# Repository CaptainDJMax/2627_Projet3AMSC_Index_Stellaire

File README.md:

## Project Description
The "Stellar Index" is an autonomous and aesthetic mechanical arm, designed to point in real time at a specific celestial object selected via a mobile or web app. Whether it's a planet, a star, the International Space Station (ISS), or a galaxy, the arm tracks the object continuously.

If the object goes below the horizon, the arm will point toward the ground. Designed with premium materials, it serves as both an educational science tool and an indoor kinetic art piece.

---

## Specifications & Technical Challenges

Here is the list of project requirements, along with recommended hardware choices and the technical challenges to anticipate.

### 1. Continuous 360° Celestial Tracking
**Description:** The arm must dynamically target a celestial object and compensate for Earth's rotation in real time, with no limits on its rotation.
- **Hardware:** A base motor for the Azimuth (horizontal) axis, a motor for the Elevation (vertical) axis, and a **slip ring** placed in the center of the rotation axis.
- **Difficulty:** Infinite rotation on the vertical axis requires a slip ring to pass the power and data cables from the base to the arm so they don't twist and snap.

### 2. Automatic Calibration via IMU and GNSS/GPS
**Description:** The user sets the object down, turns it on, and the system automatically determines its location, exact time, and spatial orientation (North, level) without manual input.
- **Hardware:** A GPS module (e.g., u-blox NEO-M8N for a quick lock) and a 9-axis Inertial Measurement Unit (IMU) with a built-in data fusion processor (e.g., BNO085 or BNO055).
- **Difficulty:** The IMU's magnetometer (compass) is extremely sensitive to ferrous metals and magnetic fields from the motors. The IMU must be placed as far away from the motors as possible (at the end of the arm), and a calibration algorithm is needed to compensate for the surrounding metal.

### 3. Easy to Transport (Foldable)
**Description:** The arm must fold down to fit into a custom carrying case.
- **Hardware:** Precision ball-bearing joints and **absolute magnetic encoders** (e.g., AS5600) on each critical axis.
- **Difficulty:** If the arm is folded while turned off, the system must know exactly what position it is in when turned back on. Absolute encoders are mandatory here because they remember the exact physical position, unlike standard relative encoders.

### 4. Elegant Design and Premium Materials (Brass)
**Description:** A high-end finish so it blends in as premium home decor.
- **Hardware:** Solid brass for the base, and anodized aluminum tubes (brass look) or brass-plated carbon fiber for the moving parts. Hidden screws.
- **Difficulty:** Brass is very dense and heavy. An arm made entirely of solid brass would require very powerful motors, which are bulky, noisy, and drain power quickly. You have to "cheat" on the moving parts by using lightweight materials that just look like brass.

### 5. Silent Operation
**Description:** The arm's movements must be virtually inaudible.
- **Hardware:** Ultra-silent motor drivers (e.g., Trinamic TMC2209 with StealthChop technology) for stepper motors, or FOC controllers (SimpleFOC) for brushless motors. Vibration dampers between the motors and the frame.
- **Difficulty:** Acoustically isolating the mechanical transmission (gears or belts). Neoprene timing belts are generally much quieter than metal gears.

### 6. Power Supply: Battery and Mains (10-hour battery life)
**Description:** Dual operation, featuring a custom built-in battery.
- **Hardware:** A Lithium-Ion cell pack (e.g., high-capacity 18650 or 21700 cells), a BMS (Battery Management System) board for safe charging/discharging, and a circuit that automatically switches between battery and wall power.
- **Difficulty:** Sizing the battery. When motors hold a position, they constantly drain energy to fight gravity. The arm must be physically balanced (by adding discreet counterweights) so the motors have to do as little work as possible.

### 7. Interface and Control
**Description:** A premium physical ON/OFF switch. The main control interface is a connected app via an API.
- **Hardware:** An **ESP32** microcontroller (which natively includes WiFi and Bluetooth BLE), and a metal toggle switch or capacitive push button integrated into the base design.
- **Difficulty:** Writing the software backend on the ESP32 so it can host a local API (an embedded web server) or seamlessly connect to the home WiFi using the user's phone Bluetooth.

### 8. Extended Offline Operation (72 hours)
**Description:** The arm must be able to track a target for 72 hours without an internet connection.
- **Hardware:** A high-precision, temperature-compensated **RTC (Real-Time Clock)** module (e.g., DS3231) with its own backup coin battery (CR2032).
- **Difficulty:** Time drift. Without the internet to resync the clock, a standard microcontroller loses several seconds a day. In astronomy, being off by just a few seconds completely ruins the pointing accuracy, making a dedicated RTC module absolutely necessary.

### 9. Interchangeable Tips
**Description:** The end of the arm can hold different attachments, like a "mechanical finger" or a laser pointer.
- **Hardware:** A quick-release connector (neodymium magnets with an alignment slot or a bayonet mount), and **Pogo Pins** (spring-loaded contacts) to send electricity to the laser module.
- **Difficulty:** Sending power to the laser tip without any visible wires, and making sure the tip always centers perfectly on the axis every time it gets swapped out.

### 10. Closed-Loop Control
**Description:** The system automatically corrects its own position errors (like if it gets bumped or misses a step).
- **Hardware:** High-resolution rotary encoders (e.g., AS5048A with 14-bit resolution) attached directly to the motor shafts.
- **Difficulty:** Software integration. You need to write a PID (Proportional, Integral, Derivative) controller into the code. This allows the microcontroller to compare where the arm *should* be with where the encoder says it *actually* is thousands of times per second, correcting the movement smoothly without making the arm shake.

---
<div align="center">
  
</div>

## Basic Electronic Stack (Summary)
* **Brain:** ESP32
* **Time & Space:** u-blox GPS, BNO085 IMU, DS3231 RTC
* **Movement:** Motors + Trinamic TMC2209 Drivers + Slip Ring
* **Position Sensors:** Absolute magnetic encoders (AS5600 / AS5048A)

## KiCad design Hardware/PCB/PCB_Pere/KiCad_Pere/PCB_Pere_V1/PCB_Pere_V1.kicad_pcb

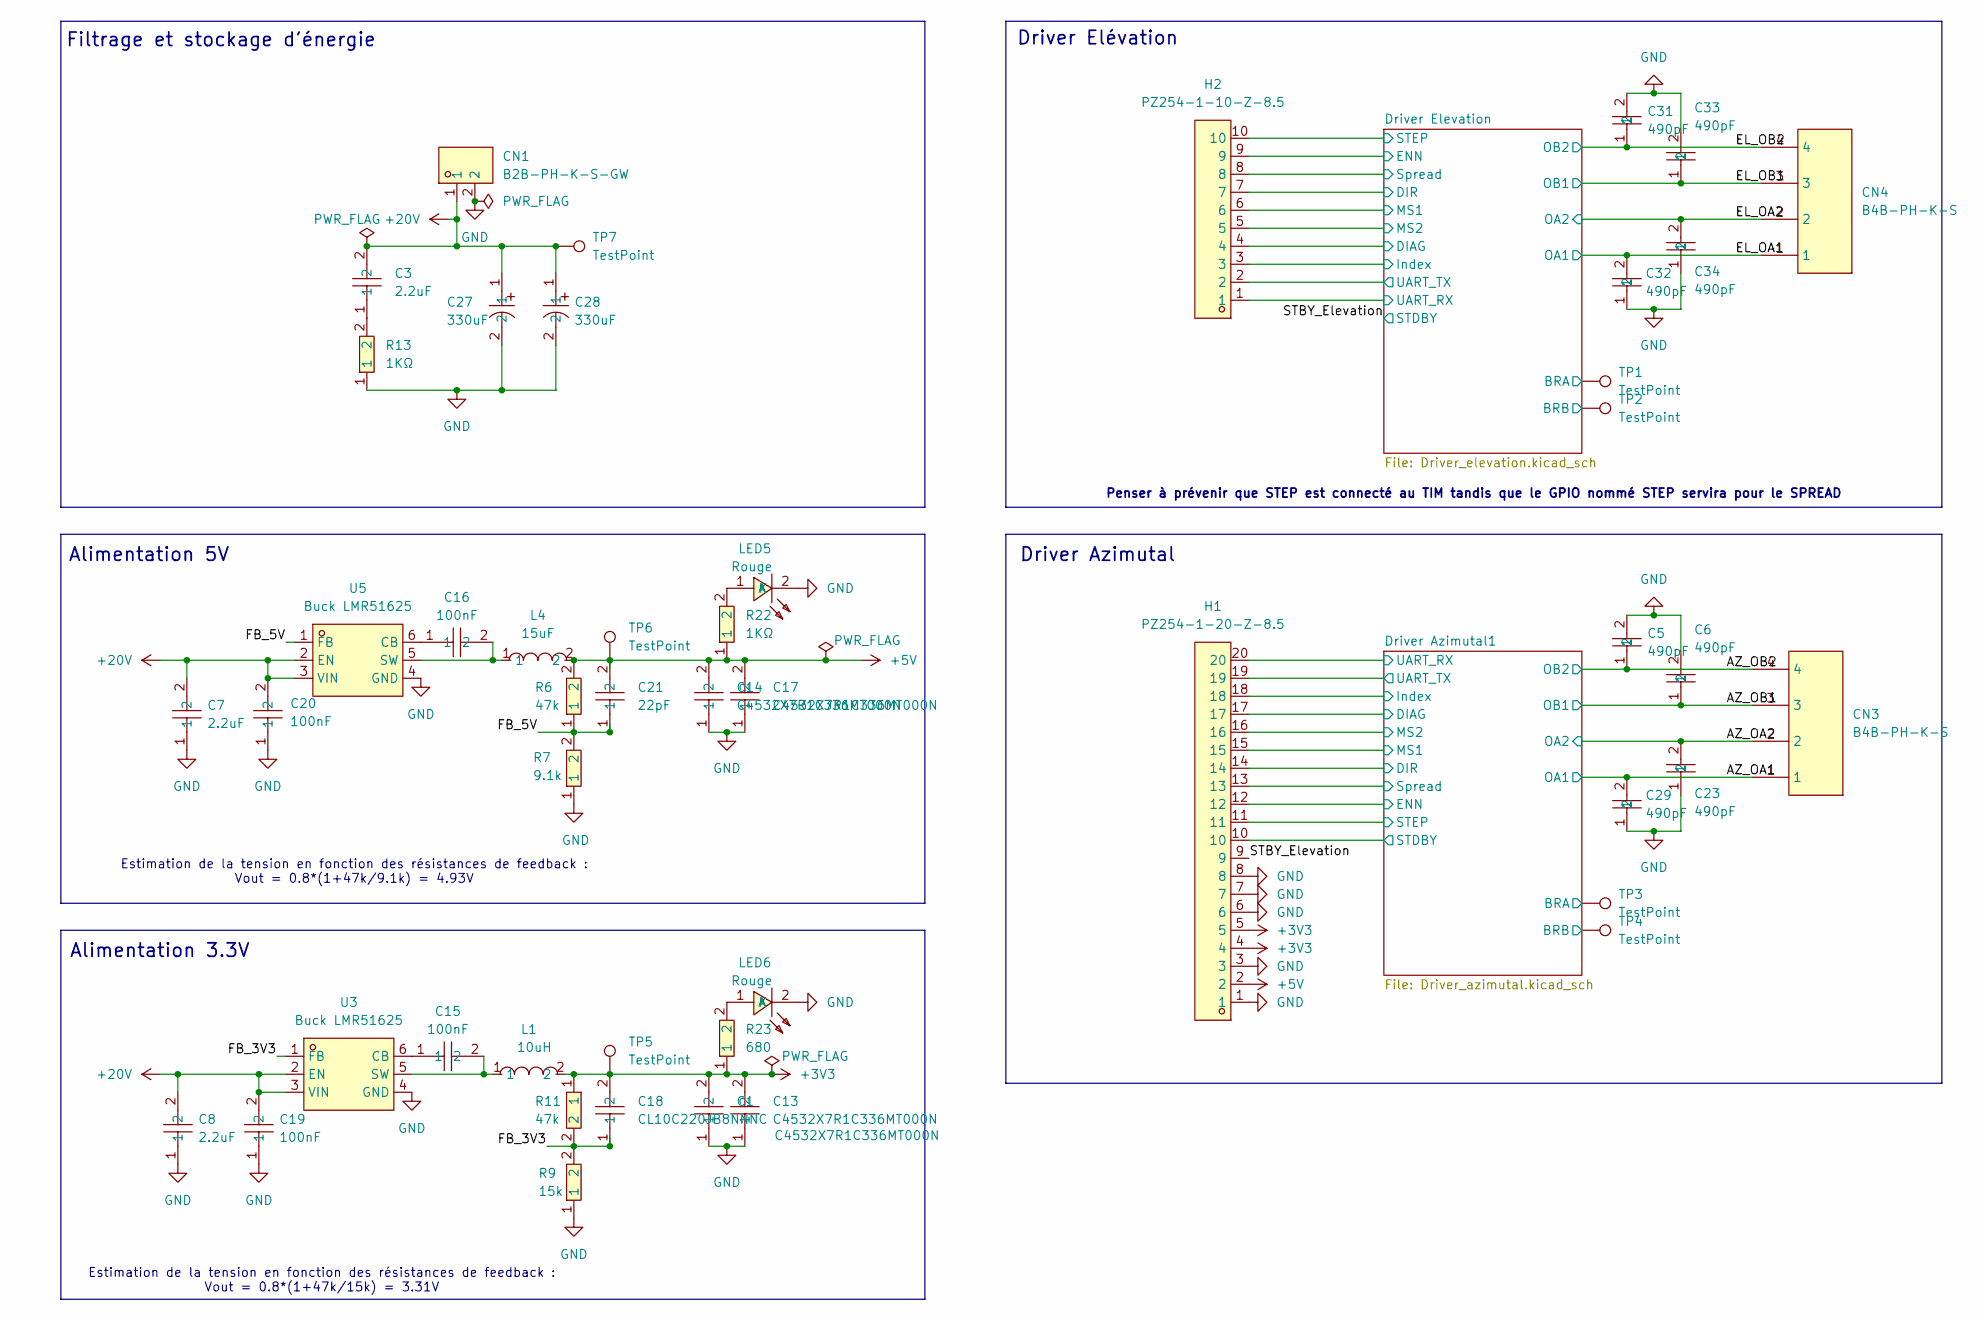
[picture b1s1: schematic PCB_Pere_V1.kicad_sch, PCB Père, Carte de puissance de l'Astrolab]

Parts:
C1, C13, C14, C17: C4532X7R1C336MT000N; C1812; MPN C4532X7R1C336MT000N; LCSC Part C342604
C3, C7, C8: 2.2uF; C1206; MPN TCC1206X7R225K500FT; LCSC Part C282852
C5, C6, C23, C29, C31, C32, C33, C34: 490pF; C0603; MPN 0603B471K500NT; LCSC Part C1620
C15, C16, C19, C20: 100nF; C0603; MPN CC0603KRX7R9BB104; LCSC Part C14663
C18: CL10C220JB8NNNC; C0603; MPN CL10C220JB8NNNC; LCSC Part C1653
C21: 22pF; C0603; MPN CL10C220JB8NNNC; LCSC Part C1653
C27, C28: 330uF; CAP-SMD_BD10.0-L10.3-W10.3-LS11.0-FD; MPN RVT1H331M1010 330UF 50V; LCSC Part C2687701
CN1: B2B-PH-K-S-GW; CONN-TH_B2B-PH-K-S; MPN B2B-PH-K-S-GW; LCSC Part C5251182
CN3, CN4: B4B-PH-K-S; CONN-TH_B4B-PH-K-S; MPN B4B-PH-K-S(LF)(SN); LCSC Part C131334
H1: PZ254-1-20-Z-8.5; HDR-TH_20P-P2.54-V-M; MPN PZ254-1-20-Z-8.5; LCSC Part C2894943
H2: PZ254-1-10-Z-8.5; HDR-TH_10P-P2.54-V-M; MPN PZ254-1-10-Z-8.5; LCSC Part C2894933
L1: 10uH; IND-SMD_L5.4-W5.2_FAUL0530-100MT; MPN FAUL0530-100MT; LCSC Part C5298168
L4: 15uF; IND-SMD_L7.0-W6.6_MCW-0650-220; MPN FAUL0630-150MT; LCSC Part C3040358
LED5, LED6: Rouge; LED-SMD_L1.6-W0.8-R-RD; MPN KT-0603R; LCSC Part C2286
R6, R11: 47k; R0603; MPN 0603WAF4702T5E; LCSC Part C23178
R7: 9.1k; R0603; MPN 0603WAF9101T5E; LCSC Part C23270
R9: 15k; R0603; MPN 0603WAF1502T5E; LCSC Part C22809
R13, R22: 1KΩ; R0603; MPN 0603WAF1001T5E; LCSC Part C21190
R23: 680; R0603; MPN 0603WAF6800T5E; LCSC Part C23228
TP1, TP2, TP3, TP4: TestPoint; TestPoint_Pad_D1.5mm
TP5, TP6, TP7: TestPoint; TestPoint_Pad_1.5x1.5mm
U3, U5: Buck LMR51625; SOT-23-6_L2.9-W1.6-P0.95-LS2.9-BL; MPN LMR51625XDDCR; LCSC Part C44750835

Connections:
+3V3: C1.2, C13.2, C18.2, H1.4, H1.5, L1.2, R11.1, R23.1, TP5.1 (1_1); also elsewhere on the board
+5V: C14.2, C17.2, C21.2, H1.2, L4.2, R6.2, R22.1, TP6.1 (1_1)
+20V: C3.2, C7.2, C8.2, C19.2, C20.2, C27.1, C28.1, CN1.1, TP7.1 (1_1), U3.2 (EN), U3.3 (VIN), U5.2 (EN), U5.3 (VIN); also elsewhere on the board
/AZ_OA1: C29.2, CN3.1; also elsewhere on the board
/AZ_OA2: C23.2, CN3.2; also elsewhere on the board
/AZ_OB1: C6.1, CN3.3; also elsewhere on the board
/AZ_OB2: C5.1, CN3.4; also elsewhere on the board
/Driver Azimutal1/BRA: TP3.1 (1_1); also elsewhere on the board
/Driver Azimutal1/BRB: TP4.1 (1_1); also elsewhere on the board
/Driver Azimutal1/DIAG: H1.17; also elsewhere on the board
/Driver Azimutal1/DIR: H1.14; also elsewhere on the board
/Driver Azimutal1/ENN: H1.12; also elsewhere on the board
/Driver Azimutal1/Index: H1.18; also elsewhere on the board
/Driver Azimutal1/MS1: H1.15; also elsewhere on the board
/Driver Azimutal1/MS2: H1.16; also elsewhere on the board
/Driver Azimutal1/STDBY: H1.10; also elsewhere on the board
/Driver Azimutal1/STEP: H1.11; also elsewhere on the board
/Driver Azimutal1/Spread: H1.13; also elsewhere on the board
/Driver Azimutal1/UART_RX: H1.20; also elsewhere on the board
/Driver Azimutal1/UART_TX: H1.19; also elsewhere on the board
/Driver Elevation/BRA: TP1.1 (1_1); also elsewhere on the board
/Driver Elevation/BRB: TP2.1 (1_1); also elsewhere on the board
/Driver Elevation/DIAG: H2.4; also elsewhere on the board
/Driver Elevation/DIR: H2.7; also elsewhere on the board
/Driver Elevation/ENN: H2.9; also elsewhere on the board
/Driver Elevation/Index: H2.3; also elsewhere on the board
/Driver Elevation/MS1: H2.6; also elsewhere on the board
/Driver Elevation/MS2: H2.5; also elsewhere on the board
/Driver Elevation/STEP: H2.10; also elsewhere on the board
/Driver Elevation/Spread: H2.8; also elsewhere on the board
/Driver Elevation/UART_RX: H2.2; also elsewhere on the board
/Driver Elevation/UART_TX: H2.1; also elsewhere on the board
/EL_OA1: C32.2, CN4.1; also elsewhere on the board
/EL_OA2: C34.2, CN4.2; also elsewhere on the board
/EL_OB1: C33.1, CN4.3; also elsewhere on the board
/EL_OB2: C31.1, CN4.4; also elsewhere on the board
/FB_3V3: C18.1, R9.2, R11.2, U3.1 (FB)
/FB_5V: C21.1, R6.1, R7.2, U5.1 (FB)
/STBY_Elevation: H1.9; also elsewhere on the board
GND: C1.1, C5.2, C6.2, C7.1, C8.1, C13.1, C14.1, C17.1, C19.1, C20.1, C23.1, C27.2, C28.2, C29.1, C31.2, C32.1, C33.2, C34.1, CN1.2, H1.1, H1.3, H1.6, H1.7, H1.8, LED5.2 (K), LED6.2 (K), R7.1, R9.1, R13.1, U3.4 (GND), U5.4 (GND); also elsewhere on the board
unnamed: C3.1, R13.2
unnamed: LED5.1 (A), R22.2
unnamed: LED6.1 (A), R23.2
unnamed: C15.1, U3.6 (CB)
unnamed: C15.2, L1.1, U3.5 (SW)
unnamed: C16.1, U5.6 (CB)
unnamed: C16.2, L4.1, U5.5 (SW)

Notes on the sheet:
Driver Azimutal
Penser à prévenir que STEP est connecté au TIM tandis que le GPIO nommé STEP servira pour le SPREAD
Driver Elévation
Alimentation 5V
Filtrage et stockage d'énergie
Estimation de la tension en fonction des résistances de feedback : Vout = 0.8*(1+47k/15k) = 3.31V
Alimentation 3.3V
Estimation de la tension en fonction des résistances de feedback : Vout = 0.8*(1+47k/9.1k) = 4.93V

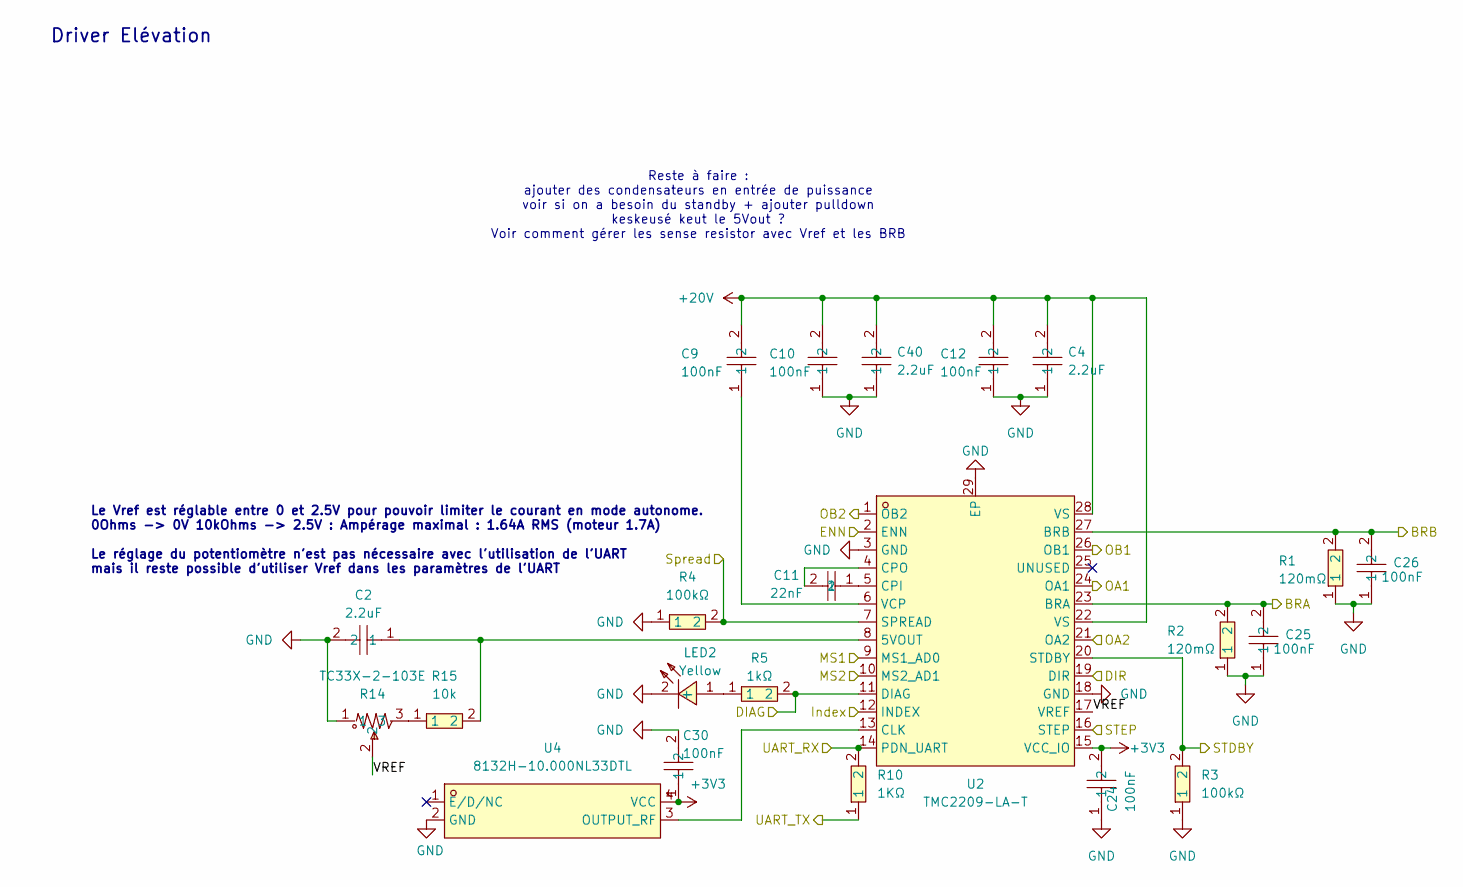
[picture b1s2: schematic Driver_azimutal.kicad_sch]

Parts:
C2, C4, C40: 2.2uF; C1206; MPN TCC1206X7R225K500FT; LCSC Part C282852
C9, C10, C12, C24, C25, C26, C30: 100nF; C0603; MPN CC0603KRX7R9BB104; LCSC Part C14663
C11: 22nF; C0805; MPN CL21B223KBANNNC; LCSC Part C1729
LED2: Yellow; LED0805-R-RD; MPN KT-0805黄灯; LCSC Part C2296
R1, R2: 120mΩ; R2512; MPN 25121WF120LT4E; LCSC Part C81248
R3, R4: 100kΩ; R0603; MPN 0603WAF1003T5E; LCSC Part C25803
R5: 1kΩ; R0603; MPN 0603WAF1001T5E; LCSC Part C21190
R10: 1KΩ; R0603; MPN 0603WAF1001T5E; LCSC Part C21190
R14: TC33X-2-103E; RES-ADJ-SMD_3P-L3.0-W3.8-P1.75-BR; MPN TC33X-2-103E; LCSC Part C719176
R15: 10k; R0603; MPN 0603WAF1002T5E; LCSC Part C25804
U2: TMC2209-LA-T; QFN-28_L5.0-W5.0-P0.50-BL-EP; MPN TMC2209-LA-T; LCSC Part C2150710
U4: 8132H-10.000NL33DTL; OSC-SMD_4P-L3.2-W2.5-BL; MPN 8132H-10.000NL33DTL; LCSC Part C46598427

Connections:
+3V3: C24.2, C30.1, U2.15 (VCC_IO), U4.4 (VCC); also elsewhere on the board
+20V: C4.2, C9.2, C10.2, C12.2, C40.2, U2.22 (VS), U2.28 (VS); also elsewhere on the board
/AZ_OA1: U2.24 (OA1); also elsewhere on the board
/AZ_OA2: U2.21 (OA2); also elsewhere on the board
/AZ_OB1: U2.26 (OB1); also elsewhere on the board
/AZ_OB2: U2.1 (OB2); also elsewhere on the board
/Driver Azimutal1/BRA: C25.2, R2.2, U2.23 (BRA); also elsewhere on the board
/Driver Azimutal1/BRB: C26.2, R1.2, U2.27 (BRB); also elsewhere on the board
/Driver Azimutal1/DIAG: R5.2, U2.11 (DIAG); also elsewhere on the board
/Driver Azimutal1/DIR: U2.19 (DIR); also elsewhere on the board
/Driver Azimutal1/ENN: U2.2 (ENN); also elsewhere on the board
/Driver Azimutal1/Index: U2.12 (INDEX); also elsewhere on the board
/Driver Azimutal1/MS1: U2.9 (MS1_AD0); also elsewhere on the board
/Driver Azimutal1/MS2: U2.10 (MS2_AD1); also elsewhere on the board
/Driver Azimutal1/STDBY: R3.2, U2.20 (STDBY); also elsewhere on the board
/Driver Azimutal1/STEP: U2.16 (STEP); also elsewhere on the board
/Driver Azimutal1/Spread: R4.2, U2.7 (SPREAD); also elsewhere on the board
/Driver Azimutal1/UART_RX: R10.2, U2.14 (PDN_UART); also elsewhere on the board
/Driver Azimutal1/UART_TX: R10.1; also elsewhere on the board
/Driver Azimutal1/VREF: R14.2, U2.17 (VREF)
GND: C2.2, C4.1, C10.1, C12.1, C24.1, C25.1, C26.1, C30.2, C40.1, LED2.2 (-), R1.1, R2.1, R3.1, R4.1, R14.1, U2.3 (GND), U2.18 (GND), U2.29 (EP), U4.2 (GND); also elsewhere on the board
unnamed: LED2.1 (+), R5.1
unnamed: R14.3, R15.1
unnamed: C2.1, R15.2, U2.8 (5VOUT)
unnamed: U2.13 (CLK), U4.3 (OUTPUT_RF)
unnamed: C11.1, U2.5 (CPI)
unnamed: C11.2, U2.4 (CPO)
unnamed: C9.1, U2.6 (VCP)

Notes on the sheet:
Le Vref est réglable entre 0 et 2.5V pour pouvoir limiter le courant en mode autonome. 0Ohms -> 0V 10kOhms -> 2.5V : Ampérage maximal : 1.64A RMS (moteur 1.7A) Le réglage du potentiomètre n'est pas nécessaire avec l'utilisation de l'UART mais il reste possible d'utiliser Vref dans les paramètres de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
Driver Elévation
Reste à faire : ajouter des condensateurs en entrée de puissance voir si on a besoin du standby + ajouter pulldown keskeusé keut le 5Vout ? Voir comment gérer les sense resistor avec Vref et les BRB

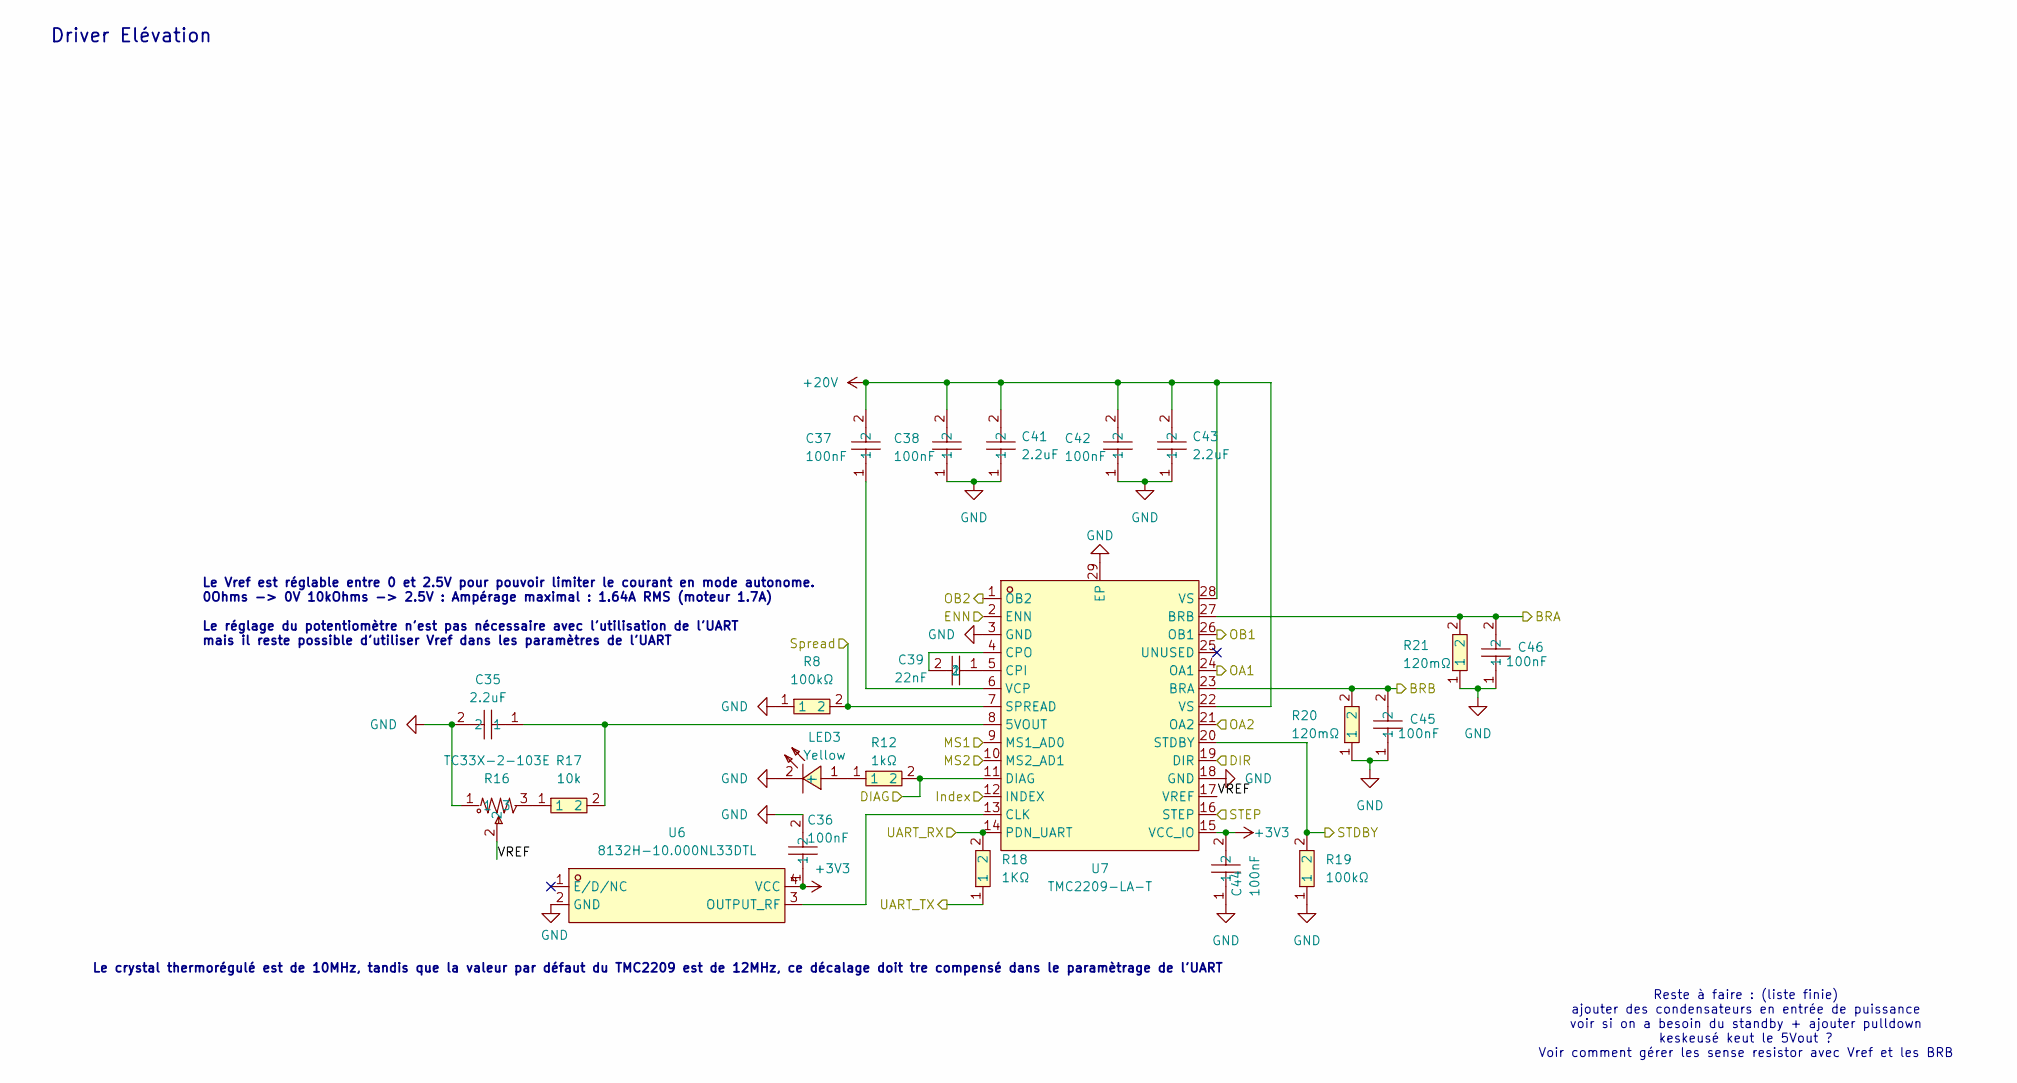
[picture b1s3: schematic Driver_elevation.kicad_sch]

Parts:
C35, C41, C43: 2.2uF; C1206; MPN TCC1206X7R225K500FT; LCSC Part C282852
C36, C37, C38, C42, C44, C45, C46: 100nF; C0603; MPN CC0603KRX7R9BB104; LCSC Part C14663
C39: 22nF; C0805; MPN CL21B223KBANNNC; LCSC Part C1729
LED3: Yellow; LED0805-R-RD; MPN KT-0805黄灯; LCSC Part C2296
R8, R19: 100kΩ; R0603; MPN 0603WAF1003T5E; LCSC Part C25803
R12: 1kΩ; R0603; MPN 0603WAF1001T5E; LCSC Part C21190
R16: TC33X-2-103E; RES-ADJ-SMD_3P-L3.0-W3.8-P1.75-BR; MPN TC33X-2-103E; LCSC Part C719176
R17: 10k; R0603; MPN 0603WAF1002T5E; LCSC Part C25804
R18: 1KΩ; R0603; MPN 0603WAF1001T5E; LCSC Part C21190
R20, R21: 120mΩ; R2512; MPN 25121WF120LT4E; LCSC Part C81248
U6: 8132H-10.000NL33DTL; OSC-SMD_4P-L3.2-W2.5-BL; MPN 8132H-10.000NL33DTL; LCSC Part C46598427
U7: TMC2209-LA-T; QFN-28_L5.0-W5.0-P0.50-BL-EP; MPN TMC2209-LA-T; LCSC Part C2150710

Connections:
+3V3: C36.1, C44.2, U6.4 (VCC), U7.15 (VCC_IO); also elsewhere on the board
+20V: C37.2, C38.2, C41.2, C42.2, C43.2, U7.22 (VS), U7.28 (VS); also elsewhere on the board
/Driver Elevation/BRA: C46.2, R21.2, U7.27 (BRB); also elsewhere on the board
/Driver Elevation/BRB: C45.2, R20.2, U7.23 (BRA); also elsewhere on the board
/Driver Elevation/DIAG: R12.2, U7.11 (DIAG); also elsewhere on the board
/Driver Elevation/DIR: U7.19 (DIR); also elsewhere on the board
/Driver Elevation/ENN: U7.2 (ENN); also elsewhere on the board
/Driver Elevation/Index: U7.12 (INDEX); also elsewhere on the board
/Driver Elevation/MS1: U7.9 (MS1_AD0); also elsewhere on the board
/Driver Elevation/MS2: U7.10 (MS2_AD1); also elsewhere on the board
/Driver Elevation/STEP: U7.16 (STEP); also elsewhere on the board
/Driver Elevation/Spread: R8.2, U7.7 (SPREAD); also elsewhere on the board
/Driver Elevation/UART_RX: R18.2, U7.14 (PDN_UART); also elsewhere on the board
/Driver Elevation/UART_TX: R18.1; also elsewhere on the board
/Driver Elevation/VREF: R16.2, U7.17 (VREF)
/EL_OA1: U7.24 (OA1); also elsewhere on the board
/EL_OA2: U7.21 (OA2); also elsewhere on the board
/EL_OB1: U7.26 (OB1); also elsewhere on the board
/EL_OB2: U7.1 (OB2); also elsewhere on the board
/STBY_Elevation: R19.2, U7.20 (STDBY); also elsewhere on the board
GND: C35.2, C36.2, C38.1, C41.1, C42.1, C43.1, C44.1, C45.1, C46.1, LED3.2 (-), R8.1, R16.1, R19.1, R20.1, R21.1, U6.2 (GND), U7.3 (GND), U7.18 (GND), U7.29 (EP); also elsewhere on the board
unnamed: LED3.1 (+), R12.1
unnamed: R16.3, R17.1
unnamed: U6.3 (OUTPUT_RF), U7.13 (CLK)
unnamed: C35.1, R17.2, U7.8 (5VOUT)
unnamed: C39.1, U7.5 (CPI)
unnamed: C39.2, U7.4 (CPO)
unnamed: C37.1, U7.6 (VCP)

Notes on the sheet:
Le Vref est réglable entre 0 et 2.5V pour pouvoir limiter le courant en mode autonome. 0Ohms -> 0V 10kOhms -> 2.5V : Ampérage maximal : 1.64A RMS (moteur 1.7A) Le réglage du potentiomètre n'est pas nécessaire avec l'utilisation de l'UART mais il reste possible d'utiliser Vref dans les paramètres de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
Le crystal thermorégulé est de 10MHz, tandis que la valeur par défaut du TMC2209 est de 12MHz, ce décalage doit tre compensé dans le paramètrage de l'UART
Driver Elévation
Reste à faire : (liste finie) ajouter des condensateurs en entrée de puissance voir si on a besoin du standby + ajouter pulldown keskeusé keut le 5Vout ? Voir comment gérer les sense resistor avec Vref et les BRB

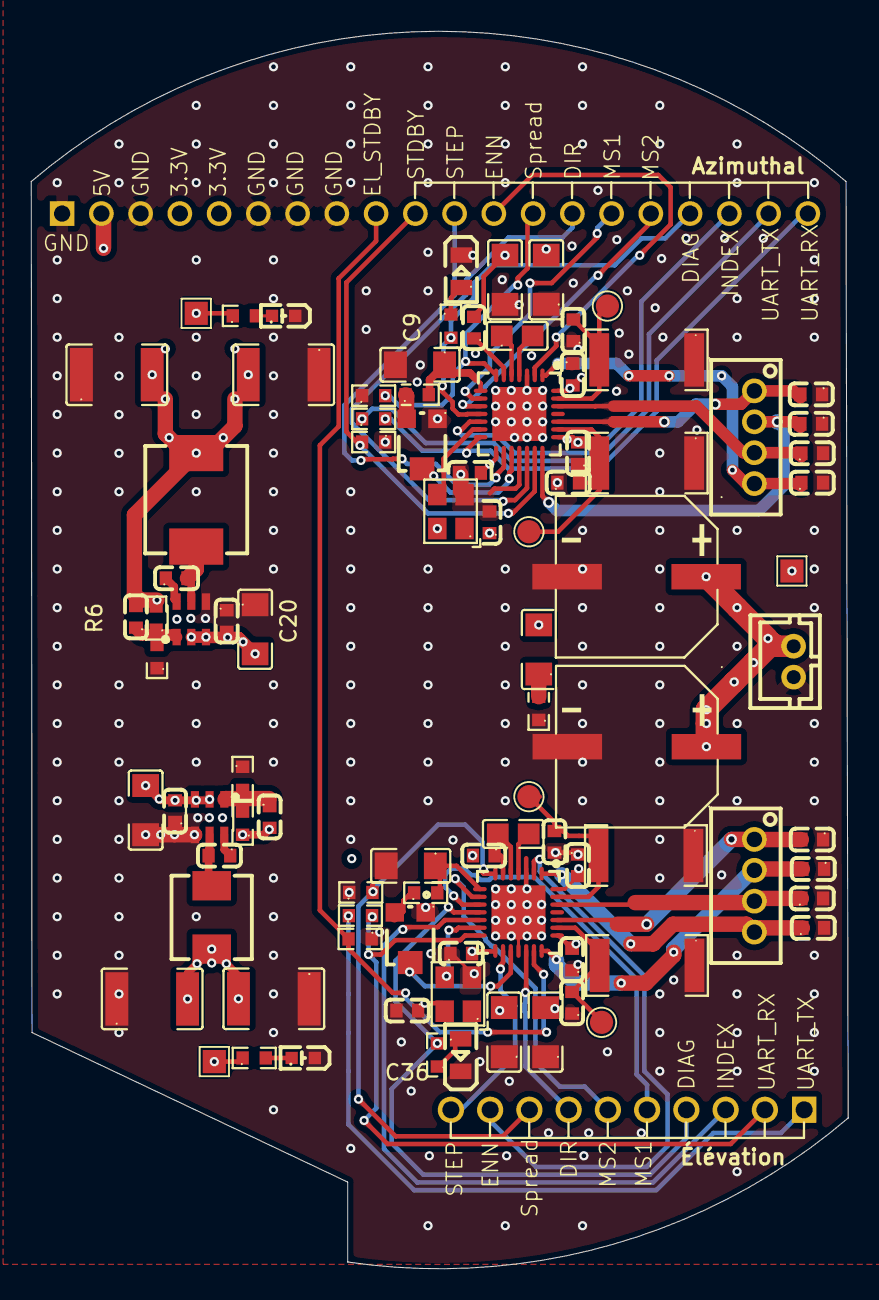
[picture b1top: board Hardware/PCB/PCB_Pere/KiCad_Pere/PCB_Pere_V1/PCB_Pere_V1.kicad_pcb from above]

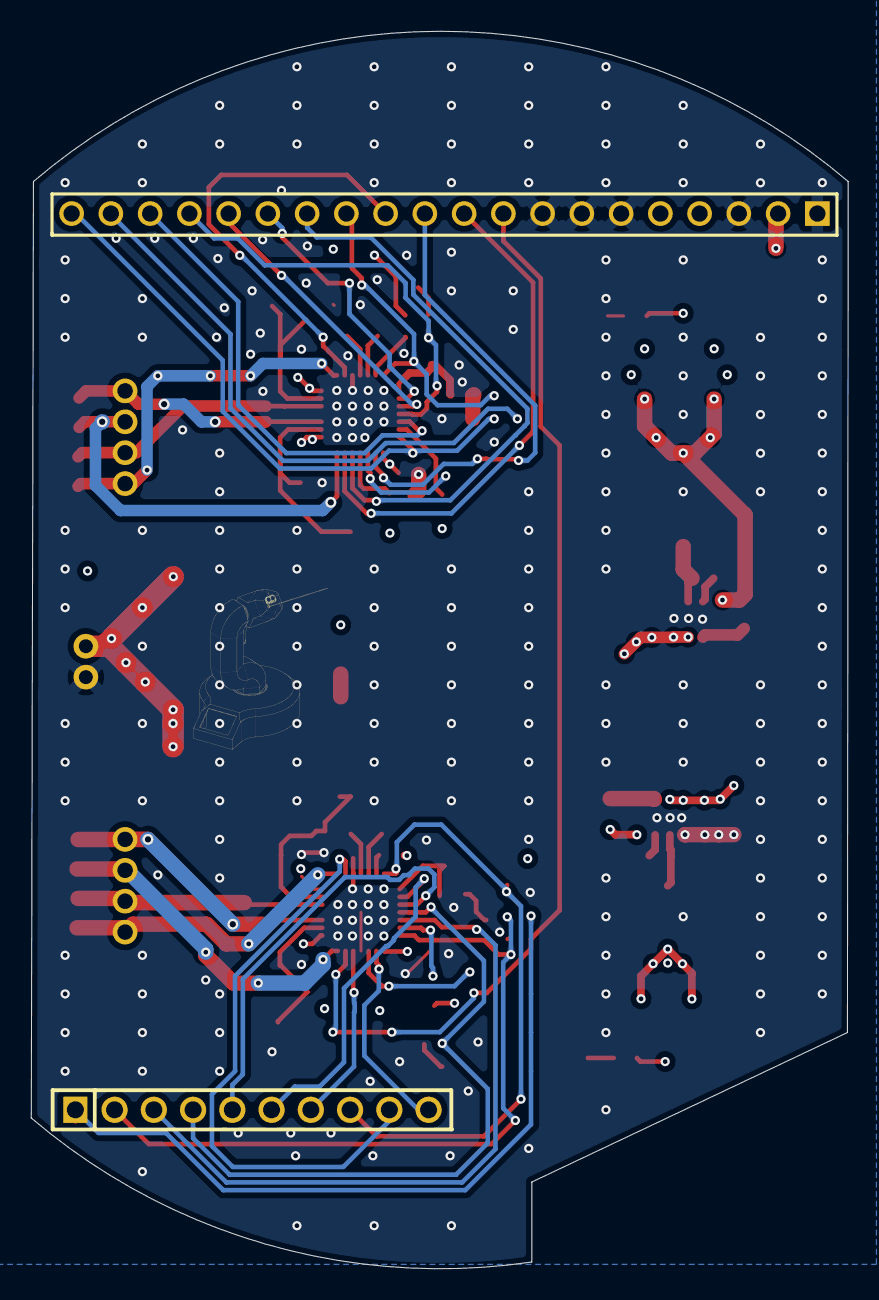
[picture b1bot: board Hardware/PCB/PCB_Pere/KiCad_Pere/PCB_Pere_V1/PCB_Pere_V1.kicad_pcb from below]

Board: 4 copper layers, 52.9 x 80.1 mm, 92 parts (2 on the bottom side), 63 nets.

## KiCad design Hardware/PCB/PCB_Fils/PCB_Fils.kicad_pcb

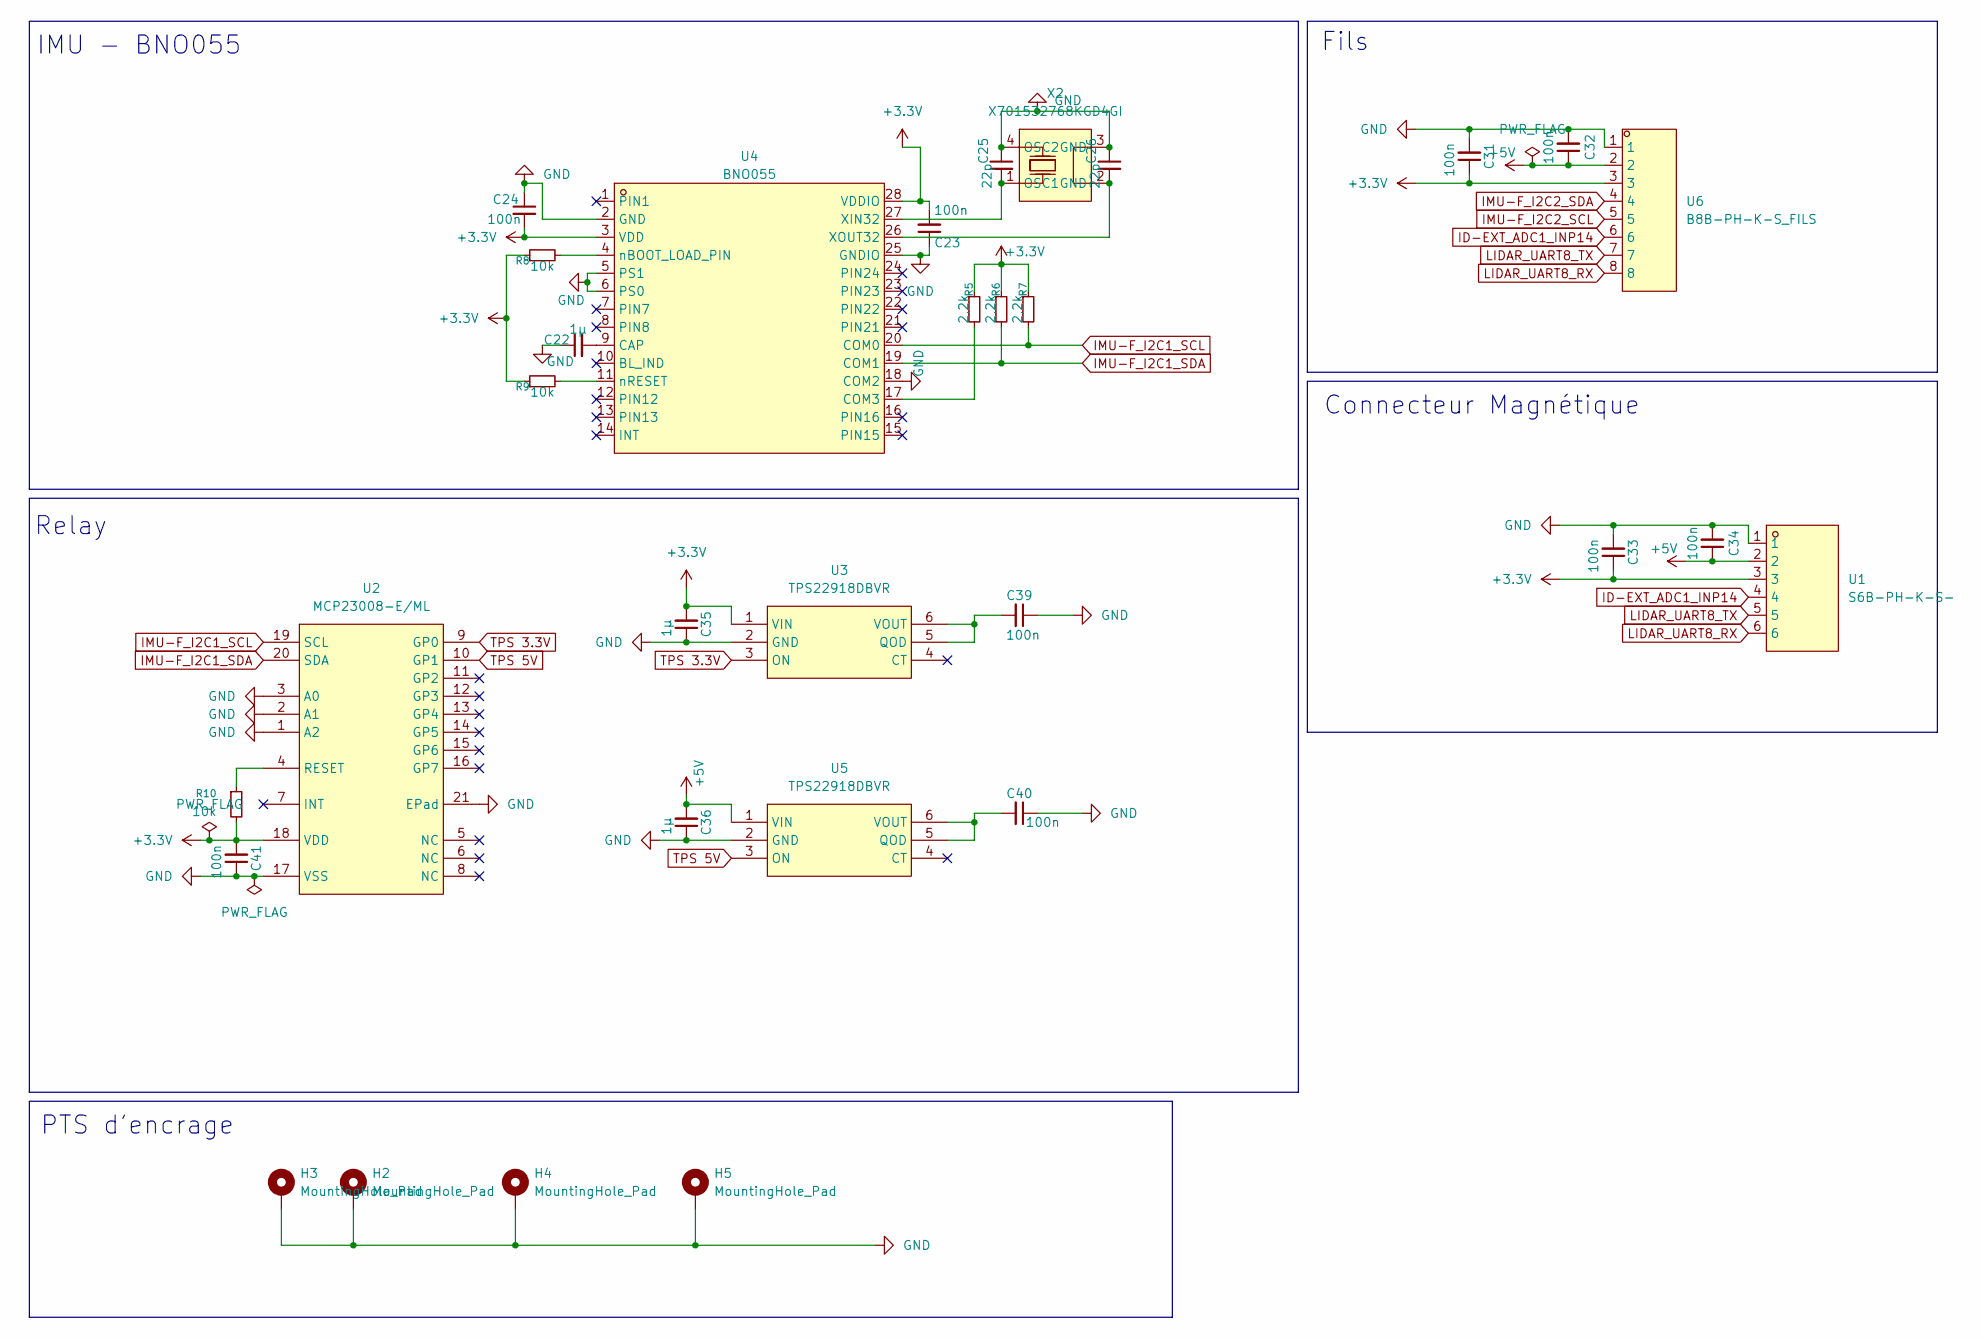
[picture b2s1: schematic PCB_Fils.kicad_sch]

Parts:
C22, C35, C36: 1µ; C_0402_1005Metric; LCSC Part C52923
C23, C24, C31, C32, C33, C34, C39, C40, C41: 100n; C_0402_1005Metric; LCSC Part C1525
C25, C26: 22p; C_0402_1005Metric; LCSC Part C1555
H2, H3, H4, H5: MountingHole_Pad; MountingHole_3.2mm_M3_DIN965_Pad_TopBottom
R5, R6, R7: 2,2k; R_0402_1005Metric; LCSC Part C25879
R8, R9, R10: 10k; R_0402_1005Metric; LCSC Part C25744
U1: S6B-PH-K-S-; CONN-TH_6P-P2.00_S6B-PH-K-S-LF-SN; MPN S6B-PH-K-S(LF)(SN); LCSC Part C157920
U2: MCP23008-E/ML; QFN-20_L4.0-W4.0-P0.50-BL-EP2.7; MPN MCP23008-E/ML; LCSC Part C144211
U3, U5: TPS22918DBVR; SOT-23-6_L2.9-W1.6-P0.95-LS2.8-BR; MPN TPS22918DBVR; LCSC Part C131941
U4: BNO055; LGA-28_L5.2-W3.8-P0.50-BL; MPN BNO055; LCSC Part C93216
U6: B8B-PH-K-S_FILS; CONN-TH_B8B-PH-K-S-LF-SN; MPN B8B-PH-K-S(LF)(SN); LCSC Part C157974
X2: X701532768KGD4GI; MC-146_4P-L6.7-W1.5-P0.85-BL; MPN X701532768KGD4GI; LCSC Part C52084

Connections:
+3.3V: C23.2, C24.2, C31.1, C33.1, C35.2, C41.2, R5.1, R6.1, R7.1, R8.1, R9.1, R10.2, U1.3, U2.18 (VDD), U3.1 (VIN), U4.3 (VDD), U4.28 (VDDIO), U6.3
+5V: C32.1, C34.1, C36.2, U1.2, U5.1 (VIN), U6.2
GND: C22.1, C23.1, C24.1, C25.1, C26.1, C31.2, C32.2, C33.2, C34.2, C35.1, C36.1, C39.1, C40.1, C41.1, H2.1 (1_1), H3.1 (1_1), H4.1 (1_1), H5.1 (1_1), U1.1, U2.1 (A2), U2.2 (A1), U2.3 (A0), U2.17 (VSS), U2.21 (EPad), U3.2 (GND), U4.2 (GND), U4.5 (PS1), U4.6 (PS0), U4.18 (COM2), U4.25 (GNDIO), U5.2 (GND), U6.1, X2.3 (GND), X2.4 (OSC2)
ID-EXT_ADC1_INP14: U1.4, U6.6
IMU-F_I2C1_SCL: R7.2, U2.19 (SCL), U4.20 (COM0)
IMU-F_I2C1_SDA: R6.2, U2.20 (SDA), U4.19 (COM1)
IMU-F_I2C2_SCL: U6.5
IMU-F_I2C2_SDA: U6.4
LIDAR_UART8_RX: U1.6, U6.8
LIDAR_UART8_TX: U1.5, U6.7
unnamed: R10.1, U2.4 (RESET)
unnamed: C39.2, U3.5 (QOD), U3.6 (VOUT)
unnamed: C22.2, U4.9 (CAP)
unnamed: R5.2, U4.17 (COM3)
unnamed: C25.2, U4.27 (XIN32), X2.1 (OSC1)
unnamed: C26.2, U4.26 (XOUT32), X2.2 (GND)
unnamed: R8.2, U4.4 (nBOOT_LOAD_PIN)
unnamed: R9.2, U4.11 (nRESET)
unnamed: C40.2, U5.5 (QOD), U5.6 (VOUT)
TPS 3.3V: U2.9 (GP0), U3.3 (ON)
TPS 5V: U2.10 (GP1), U5.3 (ON)

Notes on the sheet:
Relay
Fils
PTS d'encrage
Connecteur Magnétique
IMU - BNO055

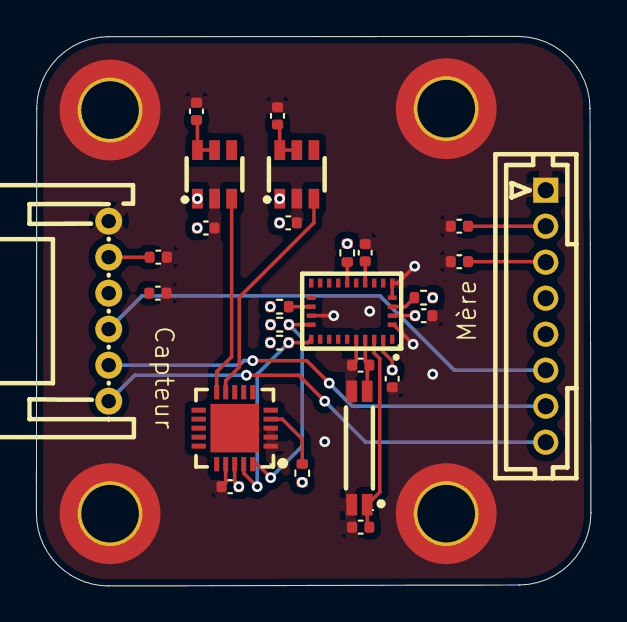
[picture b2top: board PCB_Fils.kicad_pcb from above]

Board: 4 copper layers, 30.8 x 30.5 mm, 31 parts (0 on the bottom side), 19 nets.
